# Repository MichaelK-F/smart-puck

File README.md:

# Smart Puck
A Zigbee sensor puck

## Current Plan:
- microcontroller: ESP32-C6-MINI-1-N4 [https://jlcpcb.com/partdetail/EspressifSystems-ESP32_C6_MINI_1N4/C5736265](https://jlcpcb.com/partdetail/EspressifSystems-ESP32_C6_MINI_1N4/C5736265)
- USB-C port: USB-TYPE-C-018 [https://jlcpcb.com/partdetail/DEALON-USB_TYPE_C018/C2927038](https://jlcpcb.com/partdetail/DEALON-USB_TYPE_C018/C2927038)
- battery/power management:
  - battery connector: S2B-PH-K-S(LF)(SN) [https://jlcpcb.com/partdetail/JST-S2B_PH_K_S_LF_SN/C173752](https://jlcpcb.com/partdetail/JST-S2B_PH_K_S_LF_SN/C173752)
  - battery (2000mAh) [https://core-electronics.com.au/polymer-lithium-ion-battery-2000mah-38459.html](https://core-electronics.com.au/polymer-lithium-ion-battery-2000mah-38459.html)
  - BQ25185 (charger/power path) [https://jlcpcb.com/partdetail/TexasInstruments-BQ25185DLHR/C19725033](https://jlcpcb.com/partdetail/TexasInstruments-BQ25185DLHR/C19725033)
  - TPS63900 (buck/boost) [https://jlcpcb.com/partdetail/TexasInstruments-TPS63900DSKR/C1518762](https://jlcpcb.com/partdetail/TexasInstruments-TPS63900DSKR/C1518762)
  - MAX17048G (fuel gauge) [https://jlcpcb.com/partdetail/2777647-MAX17048GT10/C2682616](https://jlcpcb.com/partdetail/2777647-MAX17048GT10/C2682616)
- led: RS-C1415MBAR [https://jlcpcb.com/partdetail/3079315-RSC1415MBAR/C2874181](https://jlcpcb.com/partdetail/3079315-RSC1415MBAR/C2874181)
- boot mode button: GT-TZ084B-H015-L1 [https://jlcpcb.com/partdetail/GSwitch-GT_TZ084B_H015L1/C29780122](https://jlcpcb.com/partdetail/GSwitch-GT_TZ084B_H015L1/C29780122)
- temperature/humidity: SHT45-AD1F-R2 [https://jlcpcb.com/partdetail/Sensirion-SHT45_AD1FR2/C5360602](https://jlcpcb.com/partdetail/Sensirion-SHT45_AD1FR2/C5360602)
- mmwave: HLK-LD2420 [https://core-electronics.com.au/human-micro-motion-detection-mmwave-sensor.html](https://core-electronics.com.au/human-micro-motion-detection-mmwave-sensor.html)
- keyboard switches for buttons (cherry mx style)
- rotary encoder (ec11?)

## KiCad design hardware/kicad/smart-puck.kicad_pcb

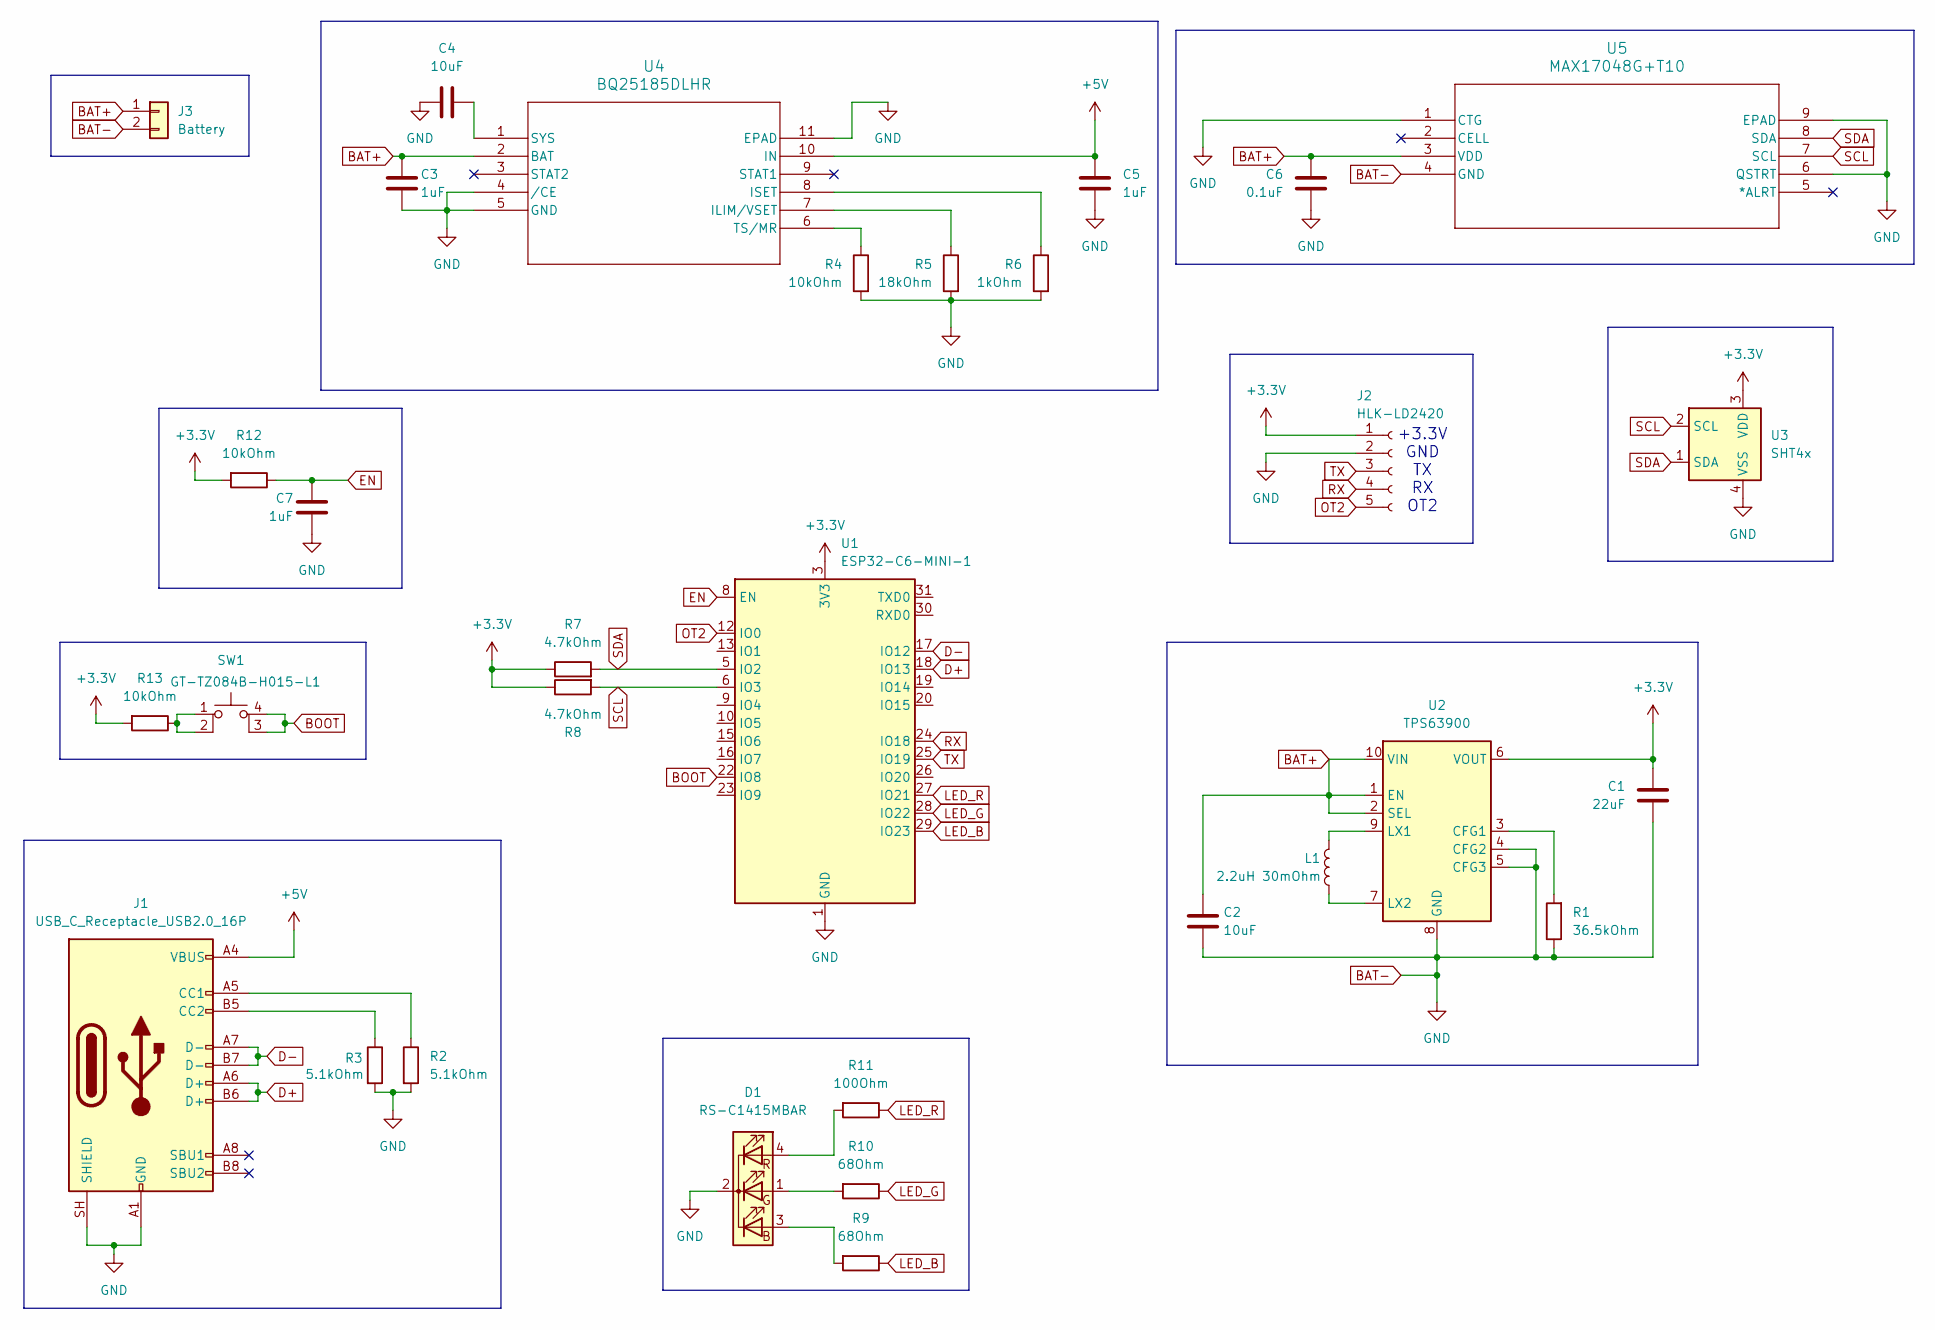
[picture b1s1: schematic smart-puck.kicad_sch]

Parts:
C1: 22uF; C_0603_1608Metric
C2, C4: 10uF; C_0603_1608Metric
C3, C5, C7: 1uF; C_0603_1608Metric
C6: 0.1uF; C_0603_1608Metric
D1: RS-C1415MBAR; LED-ARRAY-SMD_4P-L1.6-W1.6-BR-RD-CW
J1: USB_C_Receptacle_USB2.0_16P; USB_C_Receptacle_G-Switch_GT-USB-7010ASV
J2: HLK-LD2420; PinSocket_1x05_P2.54mm_Vertical
J3: Battery; JST_PH_S2B-PH-K_1x02_P2.00mm_Horizontal
L1: 2.2uH 30mOhm; L_TechFuse_SL0624
R1: 36.5kOhm; R_0402_1005Metric
R2, R3: 5.1kOhm; R_0402_1005Metric
R4, R12, R13: 10kOhm; R_0805_2012Metric
R5: 18kOhm; R_0603_1608Metric
R6: 1kOhm; R_0603_1608Metric
R7, R8: 4.7kOhm; R_0402_1005Metric
R9, R10: 68Ohm; R_0402_1005Metric
R11: 100Ohm; R_0402_1005Metric
SW1: GT-TZ084B-H015-L1; SW-SMD_4P-L5.2-W5.2-P3.70-LS6.4
U1: ESP32-C6-MINI-1
U2: TPS63900; WSON-10-1EP_2.5x2.5mm_P0.5mm_EP1.2x2mm_ThermalVias
U3: SHT4x; Sensirion_DFN-4_1.5x1.5mm_P0.8mm_SHT4x_NoCentralPad
U4: BQ25185DLHR; WSON10_DLH_TEX
U5: MAX17048G+T10; 21-0168E_T822-3_MXM

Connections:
+3.3V: C1.2, J2.1, R7.1, R8.1, R12.2, R13.2, U1.3 (3V3), U2.6 (VOUT), U3.3 (VDD)
+5V: C5.1, J1.A4 (VBUS), J1.A9 (VBUS), J1.B4 (VBUS), J1.B9 (VBUS), U4.10 (IN)
BAT+: C2.2, C3.1, C6.1, J3.1, U2.1 (EN), U2.2 (SEL), U2.10 (VIN), U4.2 (BAT), U5.3 (VDD)
BAT-: C1.1, C2.1, C3.2, C4.1, C5.2, C6.2, C7.2, D1.2 (K), J1.A1 (GND), J1.A12 (GND), J1.B1 (GND), J1.B12 (GND), J1.SH (SHIELD), J2.2, J3.2, R1.1, R2.2, R3.2, R4.2, R5.2, R6.2, U1.1 (GND), U1.2 (GND), U1.11 (GND), U1.14 (GND), U1.36 (GND), U1.37 (GND), U1.38 (GND), U1.39 (GND), U1.40 (GND), U1.41 (GND), U1.42 (GND), U1.43 (GND), U1.44 (GND), U1.45 (GND), U1.46 (GND), U1.47 (GND), U1.48 (GND), U1.49 (GND), U1.50 (GND), U1.51 (GND), U1.52 (GND), U1.53 (GND), U2.4 (CFG2), U2.5 (CFG3), U2.8 (GND), U2.11 (GND), U3.4 (VSS), U4.4 (/CE), U4.5 (GND), U4.11 (EPAD), U5.1 (CTG), U5.4 (GND), U5.6 (QSTRT), U5.9 (EPAD)
BOOT: SW1.3 (K), SW1.4 (A), U1.22 (IO8)
D+: J1.A6 (D+), J1.B6 (D+), U1.18 (IO13)
D-: J1.A7 (D-), J1.B7 (D-), U1.17 (IO12)
EN: C7.1, R12.1, U1.8 (EN)
LED_B: R9.1, U1.29 (IO23)
LED_G: R10.1, U1.28 (IO22)
LED_R: R11.1, U1.27 (IO21)
unnamed: D1.3 (BA), R9.2
unnamed: D1.1 (GA), R10.2
unnamed: D1.4 (RA), R11.2
unnamed: J1.A5 (CC1), R2.1
unnamed: J1.B5 (CC2), R3.1
unnamed: R13.1, SW1.1, SW1.2
unnamed: R1.2, U2.3 (CFG1)
unnamed: L1.2, U2.9 (LX1)
unnamed: L1.1, U2.7 (LX2)
unnamed: R5.1, U4.7 (ILIM/VSET)
unnamed: R6.1, U4.8 (ISET)
unnamed: C4.2, U4.1 (SYS)
unnamed: R4.1, U4.6 (TS/MR)
OT2: J2.5, U1.12 (IO0)
RX: J2.4, U1.24 (IO18)
SCL: R8.2, U1.6 (IO3), U3.2 (SCL), U5.7 (SCL)
SDA: R7.2, U1.5 (IO2), U3.1 (SDA), U5.8 (SDA)
TX: J2.3, U1.25 (IO19)

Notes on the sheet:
+3.3V GND TX RX OT2

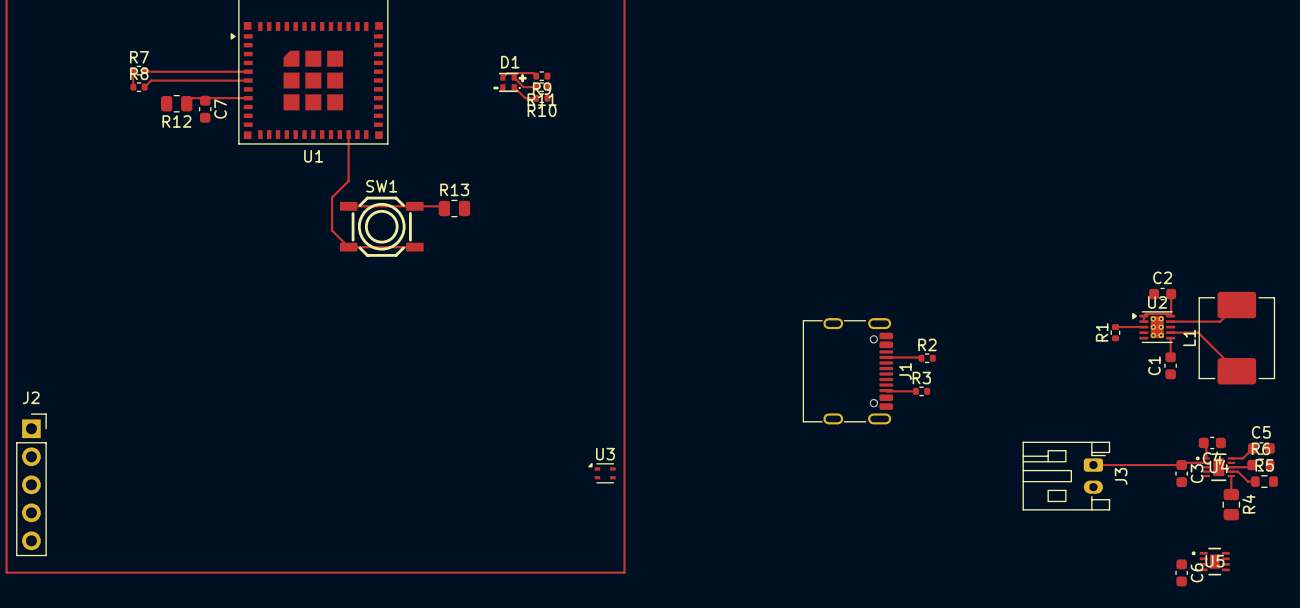
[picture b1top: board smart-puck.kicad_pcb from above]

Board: 2 copper layers, 31 parts (0 on the bottom side), 29 nets.
